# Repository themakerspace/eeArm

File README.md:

# eeArm
eeArm mini wireless robot arm
based on "meArm" but upgraded to run on ESP8266 (hence "Ee"Arm) and allow smartphone control via wifi

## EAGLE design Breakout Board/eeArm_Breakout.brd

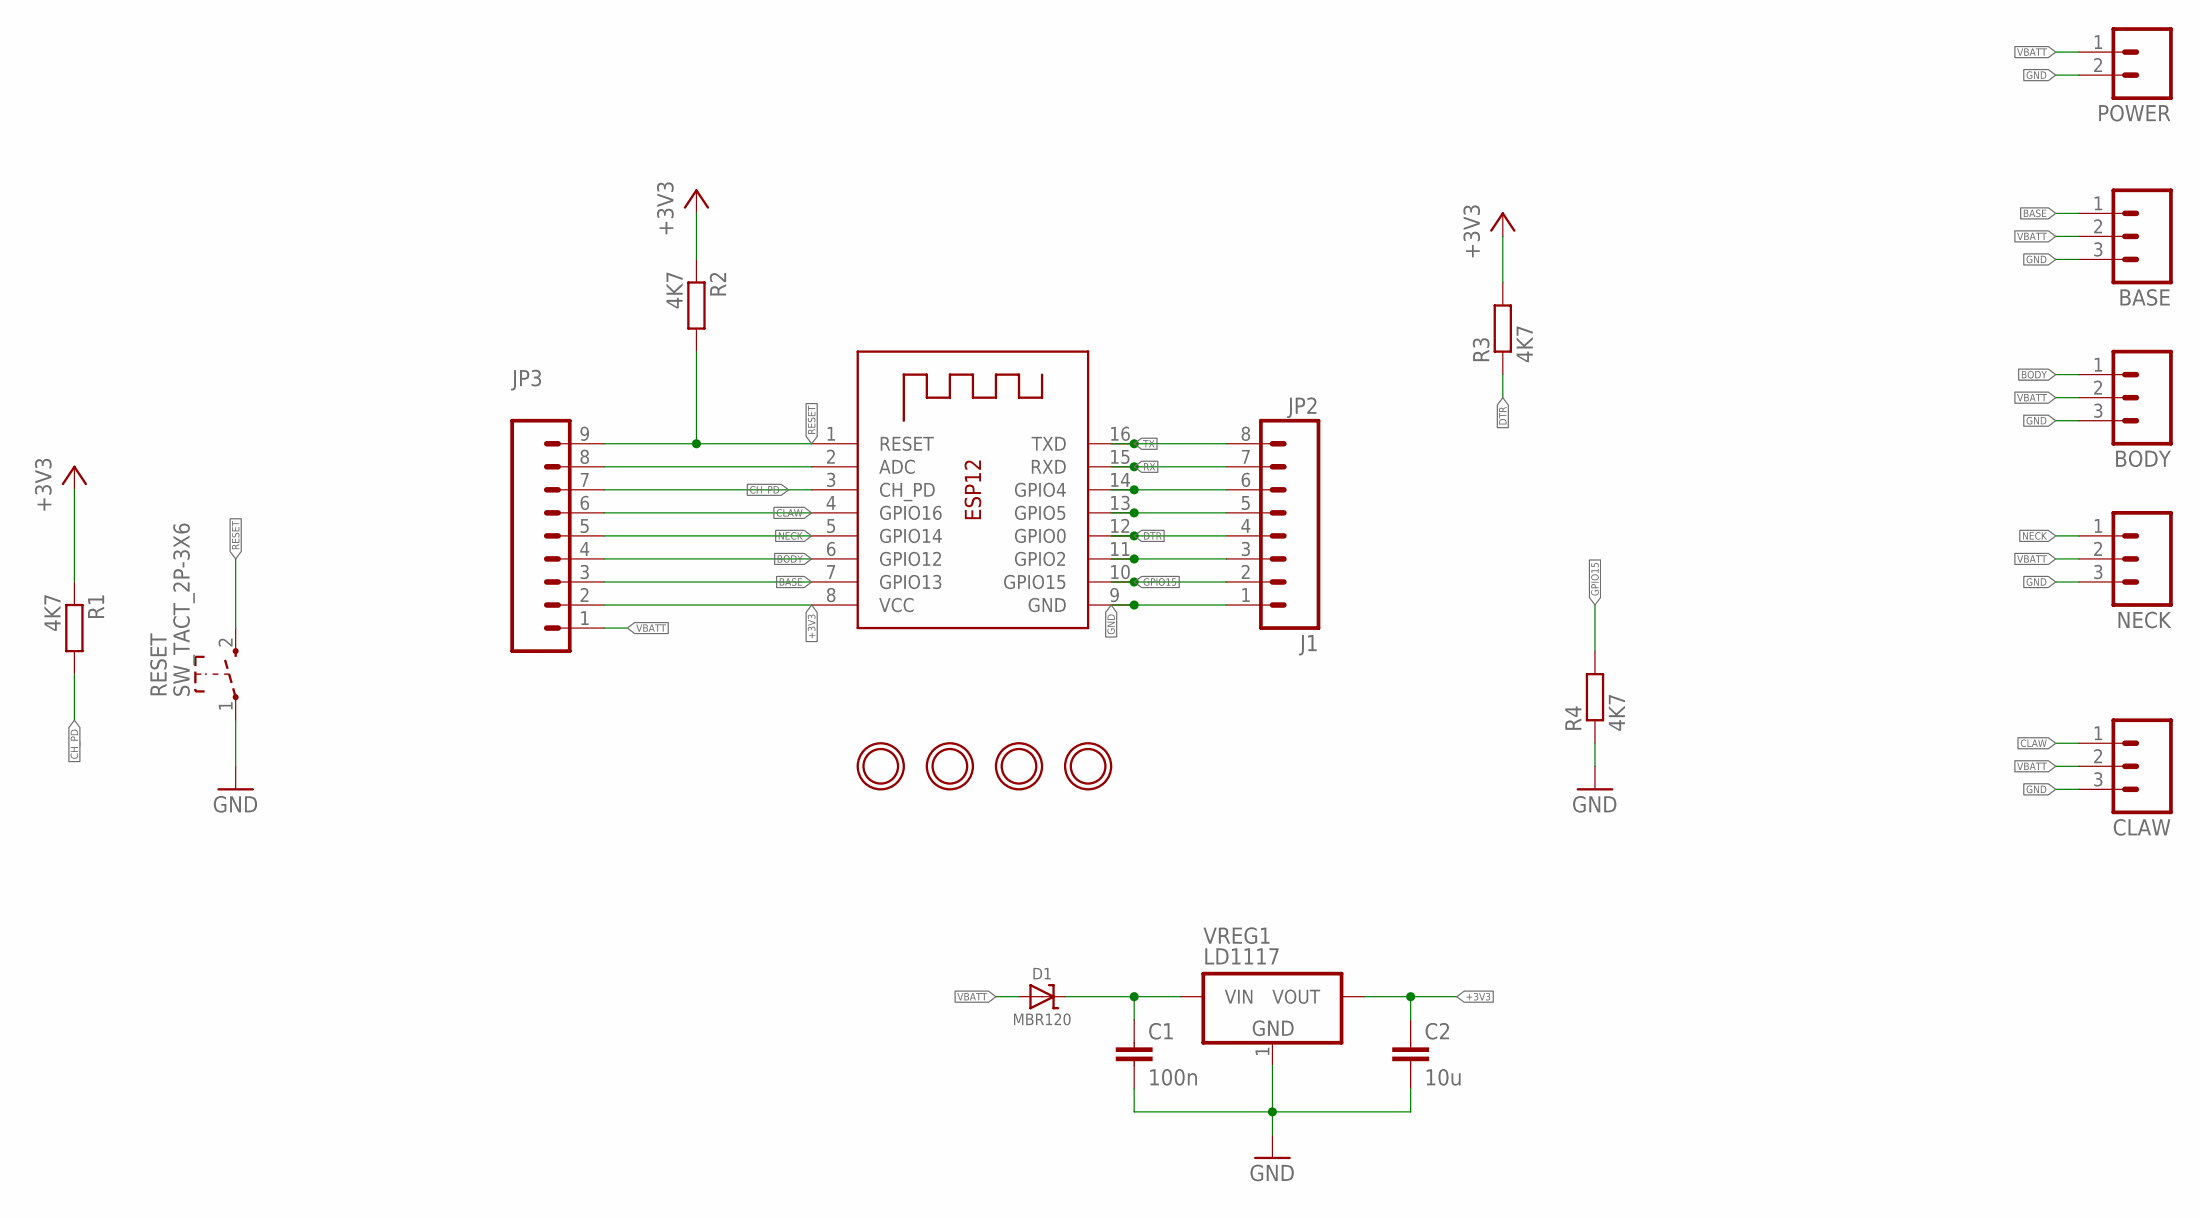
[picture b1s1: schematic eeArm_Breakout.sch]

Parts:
BASE: M03LOCK; 1X03_LOCK
BODY: M03LOCK; 1X03_LOCK
C1: 100n; C0805
C2: 10u; C0805
CLAW: M03LOCK; 1X03_LOCK
D1: MBR120; SOD-123
JP2: J1; 1X08_LOCK
JP3: M09LOCK; 1X09_LOCK
NECK: M03LOCK; 1X03_LOCK
POWER: M02LOCK; 1X02_LOCK
R1, R2, R3, R4: 4K7; R0805
RESET: SW_TACT_2P-3X6; SW_TACT_3X6
U$6, U$7, U$8, U$9: MOUNTINGHOLE2.0; MOUNTINGHOLE_2.0_PLATED
VREG1: LD1117; SOT-223
X1: ESP8266; ESP-12-NOPLACE

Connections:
+3V3: C2.1, JP3.2, R1.1, R2.1, R3.2, VREG1.2 (VOUT), X1.8 (VCC)
ADC: JP3.8, X1.2 (ADC)
BASE: BASE.1, JP3.3, X1.7 (GPIO13)
BODY: BODY.1, JP3.4, X1.6 (GPIO12)
CH_PD: JP3.7, R1.2, X1.3 (CH_PD)
CLAW: CLAW.1, JP3.6, X1.4 (GPIO16)
DTR: JP2.4, R3.1, X1.12 (GPIO0)
GND: BASE.3, BODY.3, C1.2, C2.2, CLAW.3, JP2.1, NECK.3, POWER.2, R4.1, RESET.1, VREG1.1 (GND), X1.9 (GND)
GPIO2: JP2.3, X1.11 (GPIO2)
GPIO4: JP2.6, X1.14 (GPIO4)
GPIO5: JP2.5, X1.13 (GPIO5)
GPIO15: JP2.2, R4.2, X1.10 (GPIO15)
NECK: JP3.5, NECK.1, X1.5 (GPIO14)
RESET: JP3.9, R2.2, RESET.2 (3), X1.1 (RESET)
RX: JP2.7, X1.15 (RXD)
TX: JP2.8, X1.16 (TXD)
VBATT: BASE.2, BODY.2, CLAW.2, D1.A, JP3.1, NECK.2, POWER.1
VIN: C1.1, D1.C, VREG1.3 (VIN)

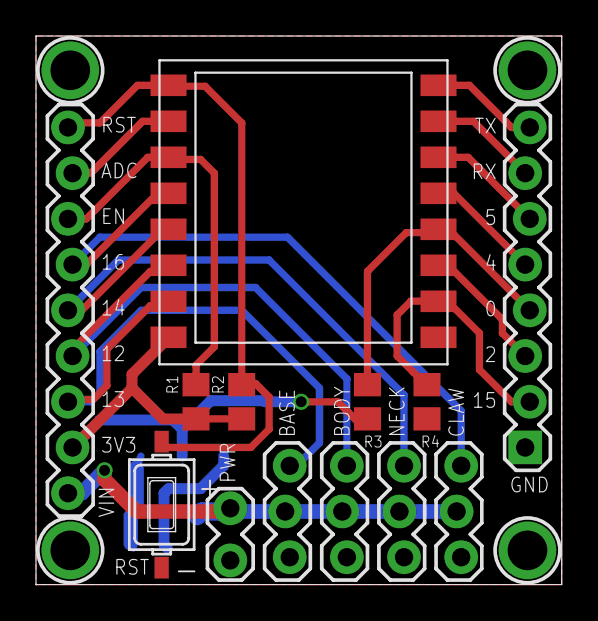
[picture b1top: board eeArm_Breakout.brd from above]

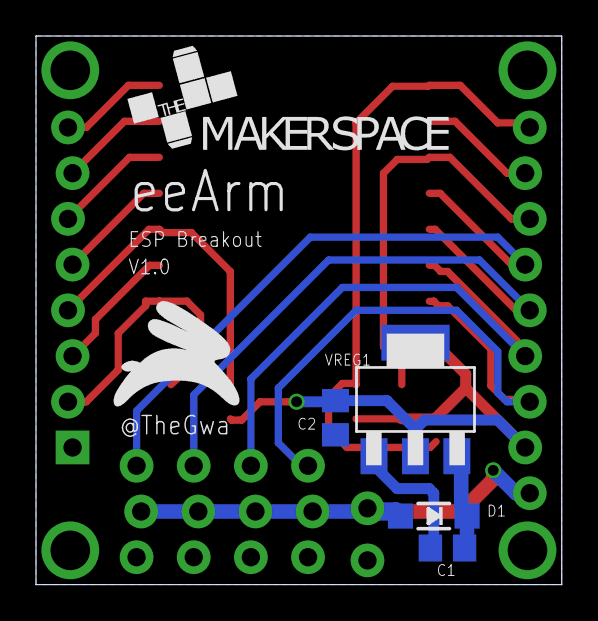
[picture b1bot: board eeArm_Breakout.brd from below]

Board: 2 copper layers, 29.2 x 30.5 mm, 23 parts (6 on the bottom side), 18 nets.

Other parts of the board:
E$1: MAKERSPACE_LOGO
E$2: GWAJA-LOGO-PLACE

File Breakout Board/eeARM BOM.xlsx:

Description | Qty | Stock Code | Part Number | Unit Price | Total
PCB | 1 |  |  | 11.111111111111111 | 11.111111111111111
RES SMD 0805 2% 10K | 4 | 65M2636-H | MCR10EZHUG103 | 0.03 | 0.12
CAP CER SMD 0805 X5R 10uF 10 | 1 | 35M0284 | C0805KKX5R6BB106 | 0.33 | 0.33
CAP CER SMD 0805 NPO 100pF 50 | 1 | 35M3582 | C0805JRNPO9BN101 | 0.3 | 0.3
DIODE SKY SOD123 20V 1A MBR120 | 1 | 35M4205 | MBR120LSFT1G | 1.29 | 1.29
REG FIX POS SOT223 3V3 1A2 | 1 | 82M0939 | LD1117S33TR | 2.0499999999999998 | 2.0499999999999998
HEADER SIL STR 40W 2.54 TH=12 | 0.5 | 64M0074 | PHSS40G1/RH | 3.21 | 1.605
SOCKET SIL STR HOUSED 2.54 40W | 0.5 | 14M6379 | FHSS40G1 | 9.84 | 4.92
Servo | 4 |  |  | 25 | 100
ESP8266 ESP-12 | 1 |  |  | 50 | 50
Screws & hardware | 1 |  |  | 30 | 30
Acrylic | 1 |  |  | ?
Laser time | 1 |  |  | ?
Total |  |  |  |  | 201.72611111111109

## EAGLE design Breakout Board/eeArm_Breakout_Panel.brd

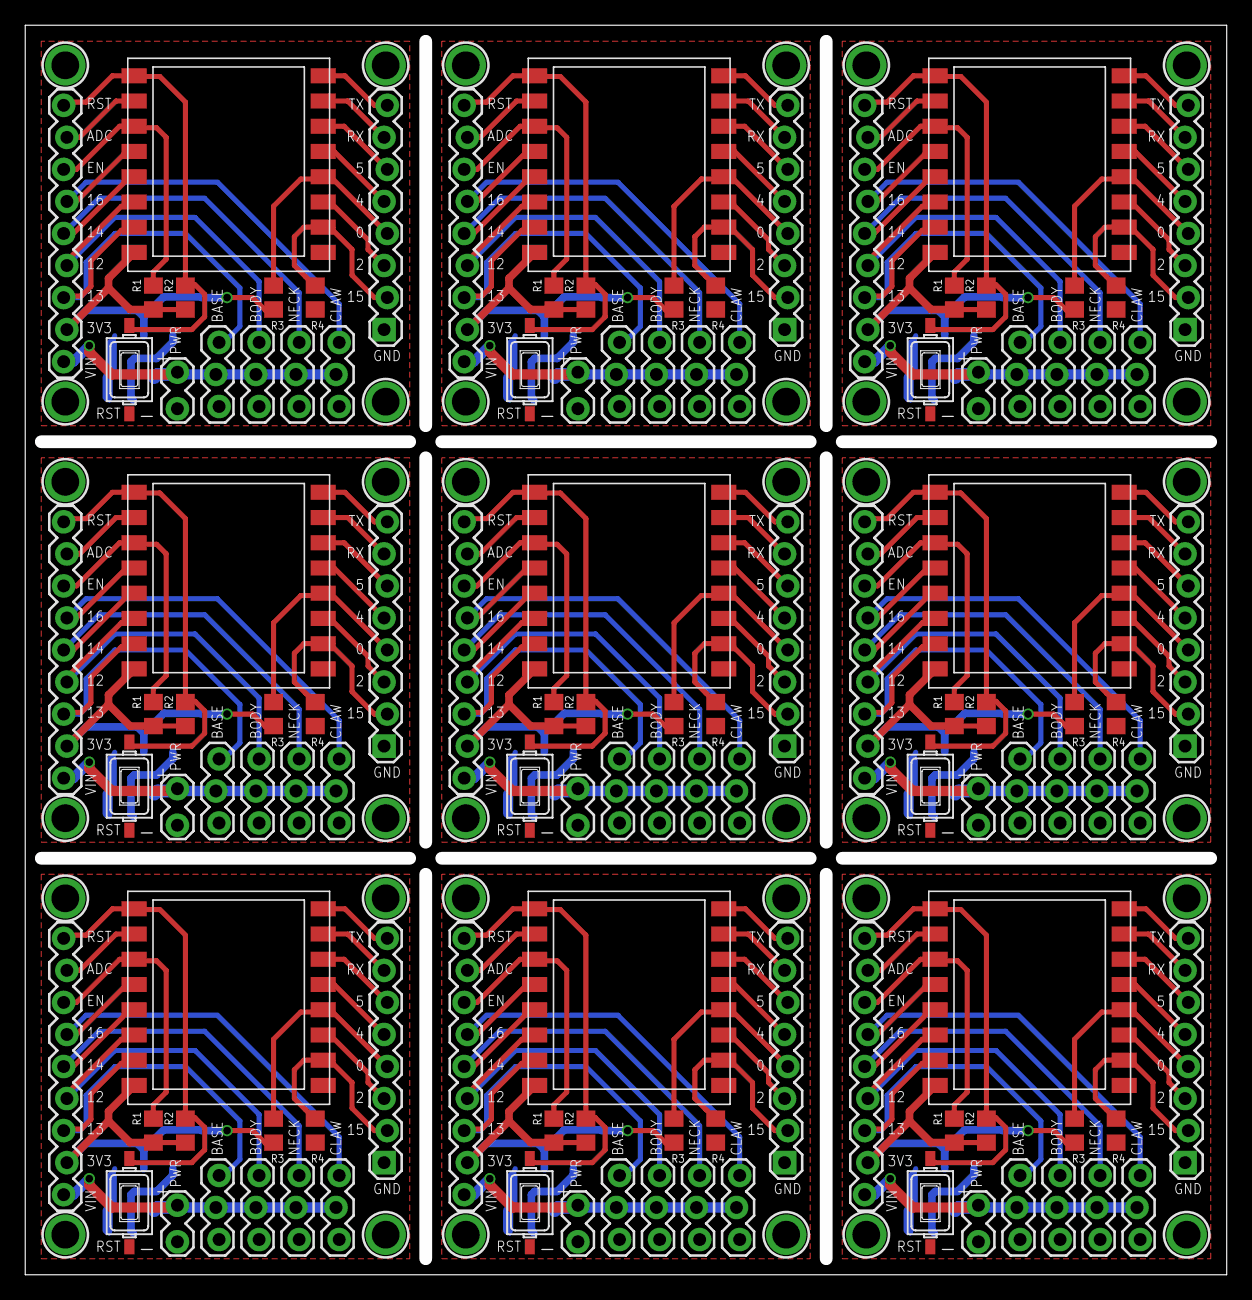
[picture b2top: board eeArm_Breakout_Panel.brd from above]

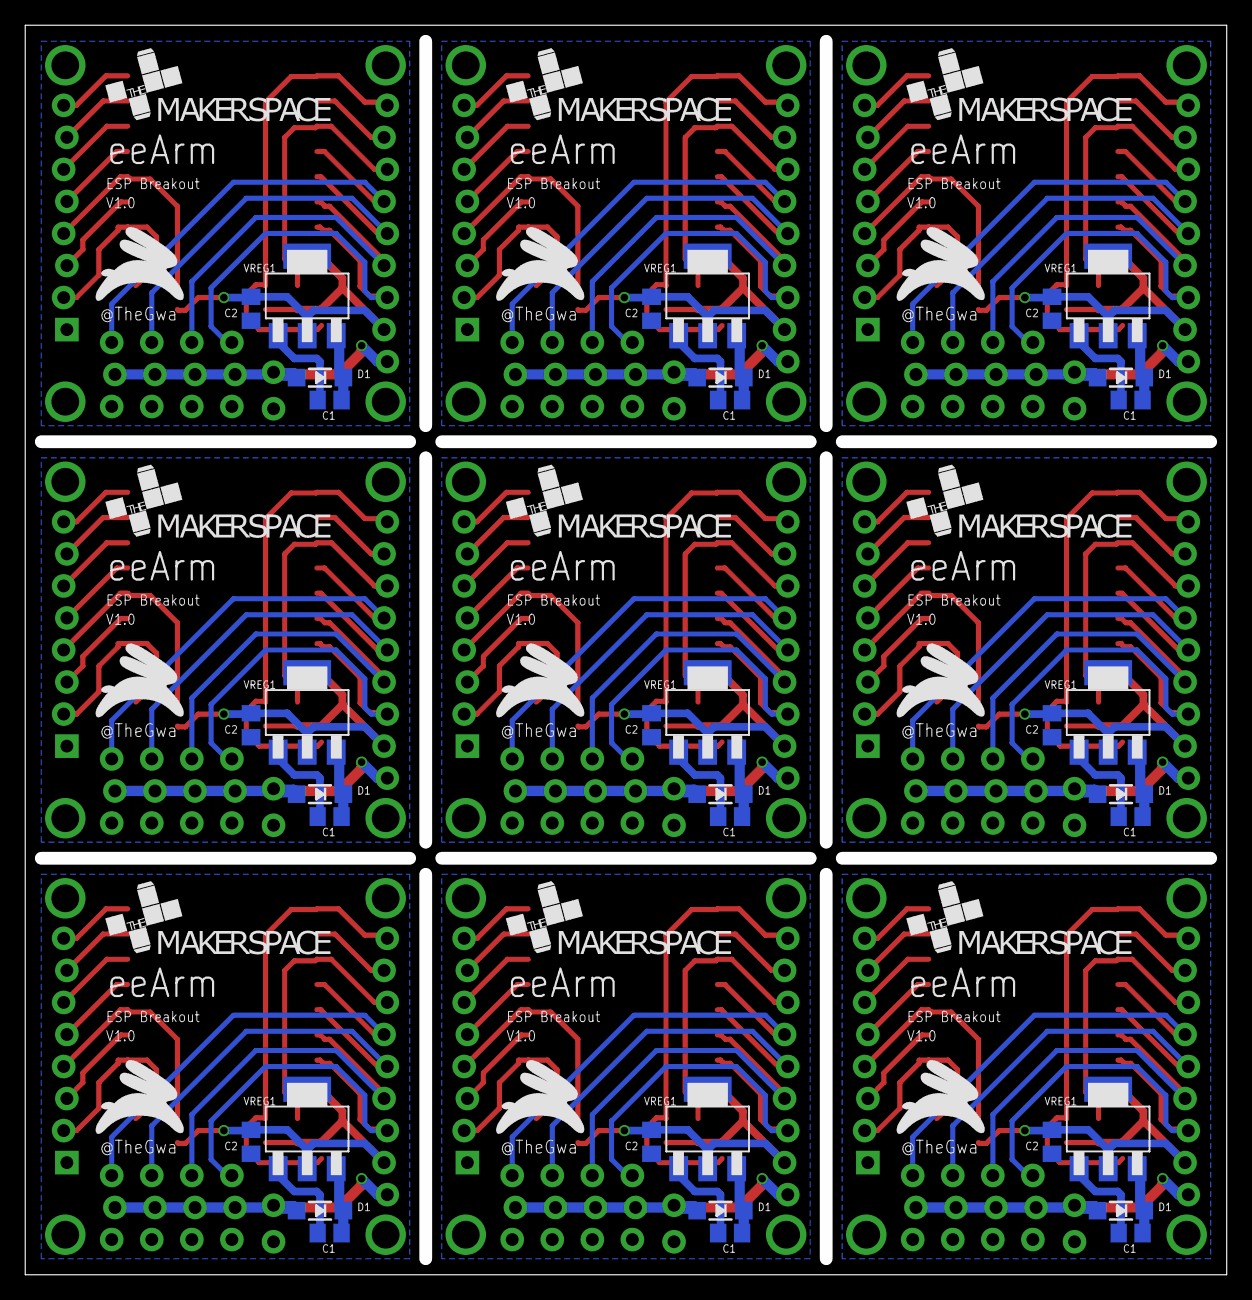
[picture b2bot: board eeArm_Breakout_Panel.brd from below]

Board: 2 copper layers, 94.2 x 98.0 mm, 207 parts (54 on the bottom side), 162 nets.

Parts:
BASE, BASE1, BASE2, BASE3, BASE4, BASE5, BASE6, BASE7, BASE8: 1X03_LOCK
BODY, BODY1, BODY2, BODY3, BODY4, BODY5, BODY6, BODY7, BODY8: 1X03_LOCK
C1, C3, C5, C7, C9, C11, C13, C15, C17: 100n; C0805
C2, C4, C6, C8, C10, C12, C14, C16, C18: 10u; C0805
CLAW, CLAW1, CLAW2, CLAW3, CLAW4, CLAW5, CLAW6, CLAW7, CLAW8: 1X03_LOCK
D1, D2, D3, D4, D5, D6, D7, D8, D9: MBR120; SOD-123
E$1, E$3, E$5, E$7, E$9, E$11, E$13, E$15, E$17: MAKERSPACE_LOGO
E$2, E$4, E$6, E$8, E$10, E$12, E$14, E$16, E$18: GWAJA-LOGO-PLACE
JP1, JP2, JP5, JP7, JP9, JP11, JP13, JP15, JP17: J1; 1X08_LOCK
JP3, JP4, JP6, JP8, JP10, JP12, JP14, JP16, JP18: 1X09_LOCK
NECK, NECK1, NECK2, NECK3, NECK4, NECK5, NECK6, NECK7, NECK8: 1X03_LOCK
POWER, POWER1, POWER2, POWER3, POWER4, POWER5, POWER6, POWER7, POWER8: 1X02_LOCK
R1, R2, R3, R4, R5, R6, R7, R8, R9, R10, R11, R12, R13, R14, R15, R16, R17, R18, R19, R20, R21, R22, R23, R24, R25, R26, R27, R28, R29, R30, R31, R32, R33, R34, R35, R36: 4K7; R0805
RESET, RESET1, RESET2, RESET3, RESET4, RESET5, RESET6, RESET7, RESET8: SW_TACT_2P-3X6; SW_TACT_3X6
U$1, U$2, U$3, U$4, U$5, U$6, U$7, U$8, U$9, U$10, U$11, U$12, U$13, U$14, U$15, U$16, U$17, U$18, U$19, U$20, U$21, U$22, U$23, U$24, U$25, U$26, U$27, U$28, U$29, U$30, U$31, U$32, U$33, U$34, U$35, U$36: MOUNTINGHOLE2.0; MOUNTINGHOLE_2.0_PLATED
VREG1, VREG2, VREG3, VREG4, VREG5, VREG6, VREG7, VREG8, VREG9: LD1117; SOT-223
X1, X2, X3, X4, X5, X6, X7, X8, X9: ESP8266; ESP-12-NOPLACE

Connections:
+3V1: C4.1, JP4.2, R6.1, R7.1, R8.2, VREG2.2, X2.8
+3V2: C6.1, JP6.2, R10.1, R11.1, R12.2, VREG3.2, X3.8
+3V3: C2.1, JP3.2, R1.1, R2.1, R3.2, VREG1.2, X1.8
+3V4: C8.1, JP8.2, R14.1, R15.1, R16.2, VREG4.2, X4.8
+3V5: C10.1, JP10.2, R18.1, R19.1, R20.2, VREG5.2, X5.8
+3V6: C12.1, JP12.2, R22.1, R23.1, R24.2, VREG6.2, X6.8
+3V7: C14.1, JP14.2, R26.1, R27.1, R28.2, VREG7.2, X7.8
+3V8: C16.1, JP16.2, R30.1, R31.1, R32.2, VREG8.2, X8.8
+3V9: C18.1, JP18.2, R34.1, R35.1, R36.2, VREG9.2, X9.8
ADC: JP3.8, X1.2
ADC1: JP4.8, X2.2
ADC2: JP6.8, X3.2
ADC3: JP8.8, X4.2
ADC4: JP10.8, X5.2
ADC5: JP12.8, X6.2
ADC6: JP14.8, X7.2
ADC7: JP16.8, X8.2
ADC8: JP18.8, X9.2
BASE: BASE.1, JP3.3, X1.7
BASE1: BASE1.1, JP4.3, X2.7
BASE2: BASE2.1, JP6.3, X3.7
BASE3: BASE3.1, JP8.3, X4.7
BASE4: BASE4.1, JP10.3, X5.7
BASE5: BASE5.1, JP12.3, X6.7
BASE6: BASE6.1, JP14.3, X7.7
BASE7: BASE7.1, JP16.3, X8.7
BASE8: BASE8.1, JP18.3, X9.7
BODY: BODY.1, JP3.4, X1.6
BODY1: BODY1.1, JP4.4, X2.6
BODY2: BODY2.1, JP6.4, X3.6
BODY3: BODY3.1, JP8.4, X4.6
BODY4: BODY4.1, JP10.4, X5.6
BODY5: BODY5.1, JP12.4, X6.6
BODY6: BODY6.1, JP14.4, X7.6
BODY7: BODY7.1, JP16.4, X8.6
BODY8: BODY8.1, JP18.4, X9.6
CH_PD: JP3.7, R1.2, X1.3
CH_PD1: JP4.7, R6.2, X2.3
CH_PD2: JP6.7, R10.2, X3.3
CH_PD3: JP8.7, R14.2, X4.3
CH_PD4: JP10.7, R18.2, X5.3
CH_PD5: JP12.7, R22.2, X6.3
CH_PD6: JP14.7, R26.2, X7.3
CH_PD7: JP16.7, R30.2, X8.3
CH_PD8: JP18.7, R34.2, X9.3
CLAW: CLAW.1, JP3.6, X1.4
CLAW1: CLAW1.1, JP4.6, X2.4
CLAW2: CLAW2.1, JP6.6, X3.4
CLAW3: CLAW3.1, JP8.6, X4.4
CLAW4: CLAW4.1, JP10.6, X5.4
CLAW5: CLAW5.1, JP12.6, X6.4
CLAW6: CLAW6.1, JP14.6, X7.4
CLAW7: CLAW7.1, JP16.6, X8.4
CLAW8: CLAW8.1, JP18.6, X9.4
DTR: JP2.4, R3.1, X1.12
DTR1: JP1.4, R8.1, X2.12
DTR2: JP5.4, R12.1, X3.12
DTR3: JP7.4, R16.1, X4.12
DTR4: JP9.4, R20.1, X5.12
DTR5: JP11.4, R24.1, X6.12
DTR6: JP13.4, R28.1, X7.12
DTR7: JP15.4, R32.1, X8.12
DTR8: JP17.4, R36.1, X9.12
GND: BASE.3, BODY.3, C1.2, C2.2, CLAW.3, JP2.1, NECK.3, POWER.2, R4.1, RESET.1, VREG1.1, X1.9
GND1: BASE1.3, BODY1.3, C3.2, C4.2, CLAW1.3, JP1.1, NECK1.3, POWER1.2, R5.1, RESET1.1, VREG2.1, X2.9
GND2: BASE2.3, BODY2.3, C5.2, C6.2, CLAW2.3, JP5.1, NECK2.3, POWER2.2, R9.1, RESET2.1, VREG3.1, X3.9
GND3: BASE3.3, BODY3.3, C7.2, C8.2, CLAW3.3, JP7.1, NECK3.3, POWER3.2, R13.1, RESET3.1, VREG4.1, X4.9
GND4: BASE4.3, BODY4.3, C9.2, C10.2, CLAW4.3, JP9.1, NECK4.3, POWER4.2, R17.1, RESET4.1, VREG5.1, X5.9
GND5: BASE5.3, BODY5.3, C11.2, C12.2, CLAW5.3, JP11.1, NECK5.3, POWER5.2, R21.1, RESET5.1, VREG6.1, X6.9
GND6: BASE6.3, BODY6.3, C13.2, C14.2, CLAW6.3, JP13.1, NECK6.3, POWER6.2, R25.1, RESET6.1, VREG7.1, X7.9
GND7: BASE7.3, BODY7.3, C15.2, C16.2, CLAW7.3, JP15.1, NECK7.3, POWER7.2, R29.1, RESET7.1, VREG8.1, X8.9
GND8: BASE8.3, BODY8.3, C17.2, C18.2, CLAW8.3, JP17.1, NECK8.3, POWER8.2, R33.1, RESET8.1, VREG9.1, X9.9
GPIO1: JP1.5, X2.13
GPIO2: JP2.3, X1.11
GPIO3: JP1.3, X2.11
GPIO4: JP2.6, X1.14
GPIO5: JP2.5, X1.13
GPIO6: JP1.6, X2.14
GPIO7: JP1.2, R5.2, X2.10
GPIO8: JP5.5, X3.13
GPIO9: JP5.3, X3.11
GPIO10: JP5.6, X3.14
GPIO11: JP5.2, R9.2, X3.10
GPIO12: JP7.5, X4.13
GPIO13: JP7.3, X4.11
GPIO14: JP7.6, X4.14
GPIO15: JP2.2, R4.2, X1.10
GPIO16: JP7.2, R13.2, X4.10
GPIO17: JP9.5, X5.13
GPIO18: JP9.3, X5.11
GPIO19: JP9.6, X5.14
GPIO20: JP9.2, R17.2, X5.10
GPIO21: JP11.5, X6.13
GPIO22: JP11.3, X6.11
GPIO23: JP11.6, X6.14
GPIO24: JP11.2, R21.2, X6.10
GPIO25: JP13.5, X7.13
GPIO26: JP13.3, X7.11
GPIO27: JP13.6, X7.14
GPIO28: JP13.2, R25.2, X7.10
GPIO29: JP15.5, X8.13
GPIO30: JP15.3, X8.11
GPIO31: JP15.6, X8.14
GPIO32: JP15.2, R29.2, X8.10
GPIO33: JP17.5, X9.13
GPIO34: JP17.3, X9.11
GPIO35: JP17.6, X9.14
GPIO36: JP17.2, R33.2, X9.10
NECK: JP3.5, NECK.1, X1.5
NECK1: JP4.5, NECK1.1, X2.5
NECK2: JP6.5, NECK2.1, X3.5
NECK3: JP8.5, NECK3.1, X4.5
NECK4: JP10.5, NECK4.1, X5.5
NECK5: JP12.5, NECK5.1, X6.5
NECK6: JP14.5, NECK6.1, X7.5
NECK7: JP16.5, NECK7.1, X8.5
NECK8: JP18.5, NECK8.1, X9.5
RESET: JP3.9, R2.2, RESET.2, X1.1
RESET1: JP4.9, R7.2, RESET1.2, X2.1
RESET2: JP6.9, R11.2, RESET2.2, X3.1
RESET3: JP8.9, R15.2, RESET3.2, X4.1
RESET4: JP10.9, R19.2, RESET4.2, X5.1
RESET5: JP12.9, R23.2, RESET5.2, X6.1
RESET6: JP14.9, R27.2, RESET6.2, X7.1
RESET7: JP16.9, R31.2, RESET7.2, X8.1
RESET8: JP18.9, R35.2, RESET8.2, X9.1
RX: JP2.7, X1.15
RX1: JP1.7, X2.15
RX2: JP5.7, X3.15
RX3: JP7.7, X4.15
RX4: JP9.7, X5.15
RX5: JP11.7, X6.15
RX6: JP13.7, X7.15
RX7: JP15.7, X8.15
RX8: JP17.7, X9.15
TX: JP2.8, X1.16
TX1: JP1.8, X2.16
TX2: JP5.8, X3.16
TX3: JP7.8, X4.16
TX4: JP9.8, X5.16
TX5: JP11.8, X6.16
TX6: JP13.8, X7.16
TX7: JP15.8, X8.16
TX8: JP17.8, X9.16
VBATT: BASE.2, BODY.2, CLAW.2, D1.A, JP3.1, NECK.2, POWER.1
VBATT1: BASE1.2, BODY1.2, CLAW1.2, D2.A, JP4.1, NECK1.2, POWER1.1
VBATT2: BASE2.2, BODY2.2, CLAW2.2, D3.A, JP6.1, NECK2.2, POWER2.1
VBATT3: BASE3.2, BODY3.2, CLAW3.2, D4.A, JP8.1, NECK3.2, POWER3.1
VBATT4: BASE4.2, BODY4.2, CLAW4.2, D5.A, JP10.1, NECK4.2, POWER4.1
VBATT5: BASE5.2, BODY5.2, CLAW5.2, D6.A, JP12.1, NECK5.2, POWER5.1
VBATT6: BASE6.2, BODY6.2, CLAW6.2, D7.A, JP14.1, NECK6.2, POWER6.1
VBATT7: BASE7.2, BODY7.2, CLAW7.2, D8.A, JP16.1, NECK7.2, POWER7.1
VBATT8: BASE8.2, BODY8.2, CLAW8.2, D9.A, JP18.1, NECK8.2, POWER8.1
VIN: C1.1, D1.C, VREG1.3
VIN1: C3.1, D2.C, VREG2.3
VIN2: C5.1, D3.C, VREG3.3
VIN3: C7.1, D4.C, VREG4.3
VIN4: C9.1, D5.C, VREG5.3
VIN5: C11.1, D6.C, VREG6.3
VIN6: C13.1, D7.C, VREG7.3
VIN7: C15.1, D8.C, VREG8.3
VIN8: C17.1, D9.C, VREG9.3

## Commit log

2015-08-12 Added first draft of breakout board
2015-08-13 Started with labels
2015-08-13 Ready for panelising
2015-08-14 Go time
2015-08-14 Added Panel
2015-08-15 Finished panalising
2015-08-15 Added BOM
2015-08-24 Completed board and added stencil

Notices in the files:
parts and their libraries:
SparkFun-Connectors: Licensing: Creative Commons ShareAlike 4.0 International - https://creativecommons.org/licenses/by-sa/4.0
